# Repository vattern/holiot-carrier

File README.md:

# holiot-carrier
Carrirer board for Holyiots to fit BastardKB housings

PLEASE NOTE: These boards have to be angled when inserting them.

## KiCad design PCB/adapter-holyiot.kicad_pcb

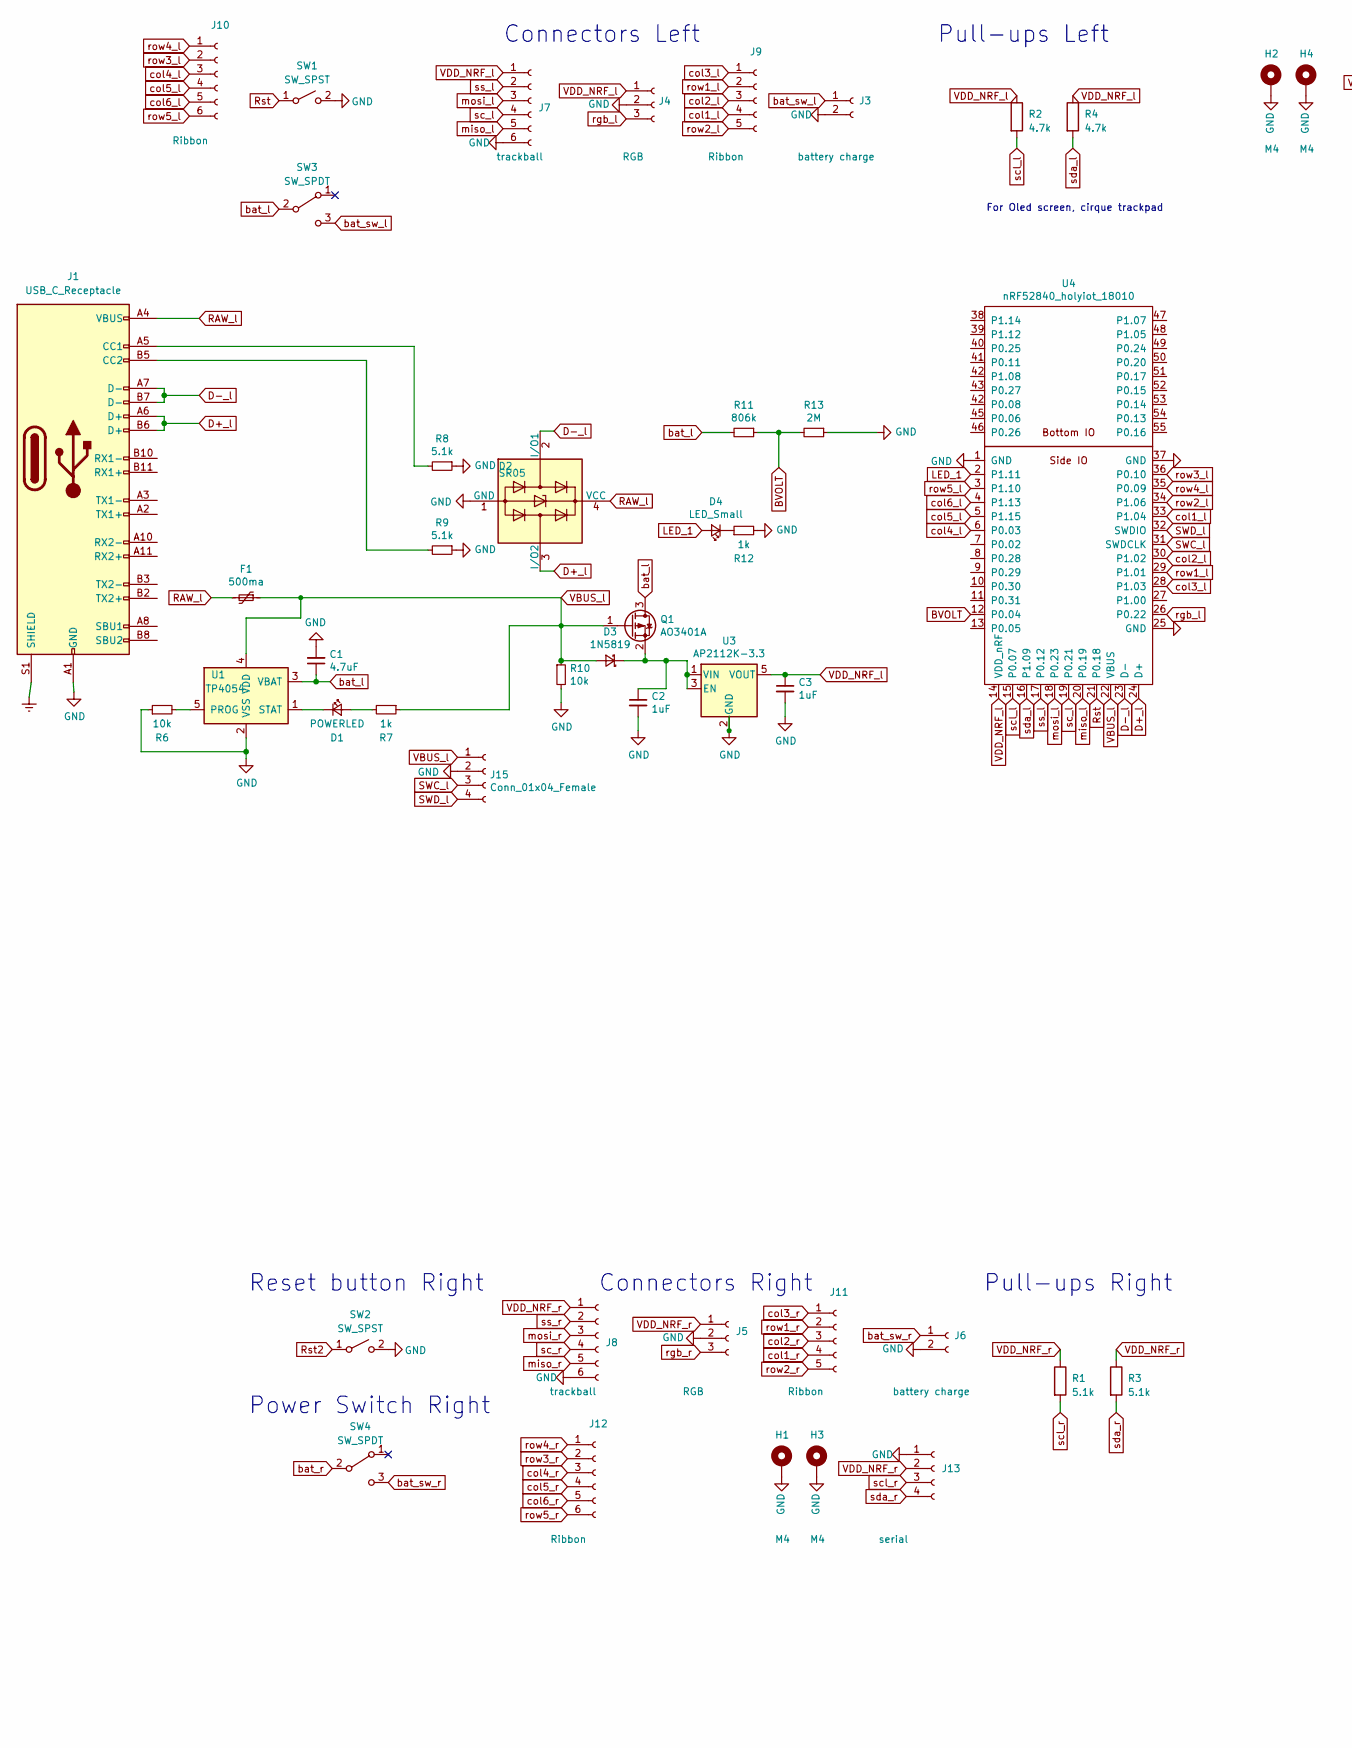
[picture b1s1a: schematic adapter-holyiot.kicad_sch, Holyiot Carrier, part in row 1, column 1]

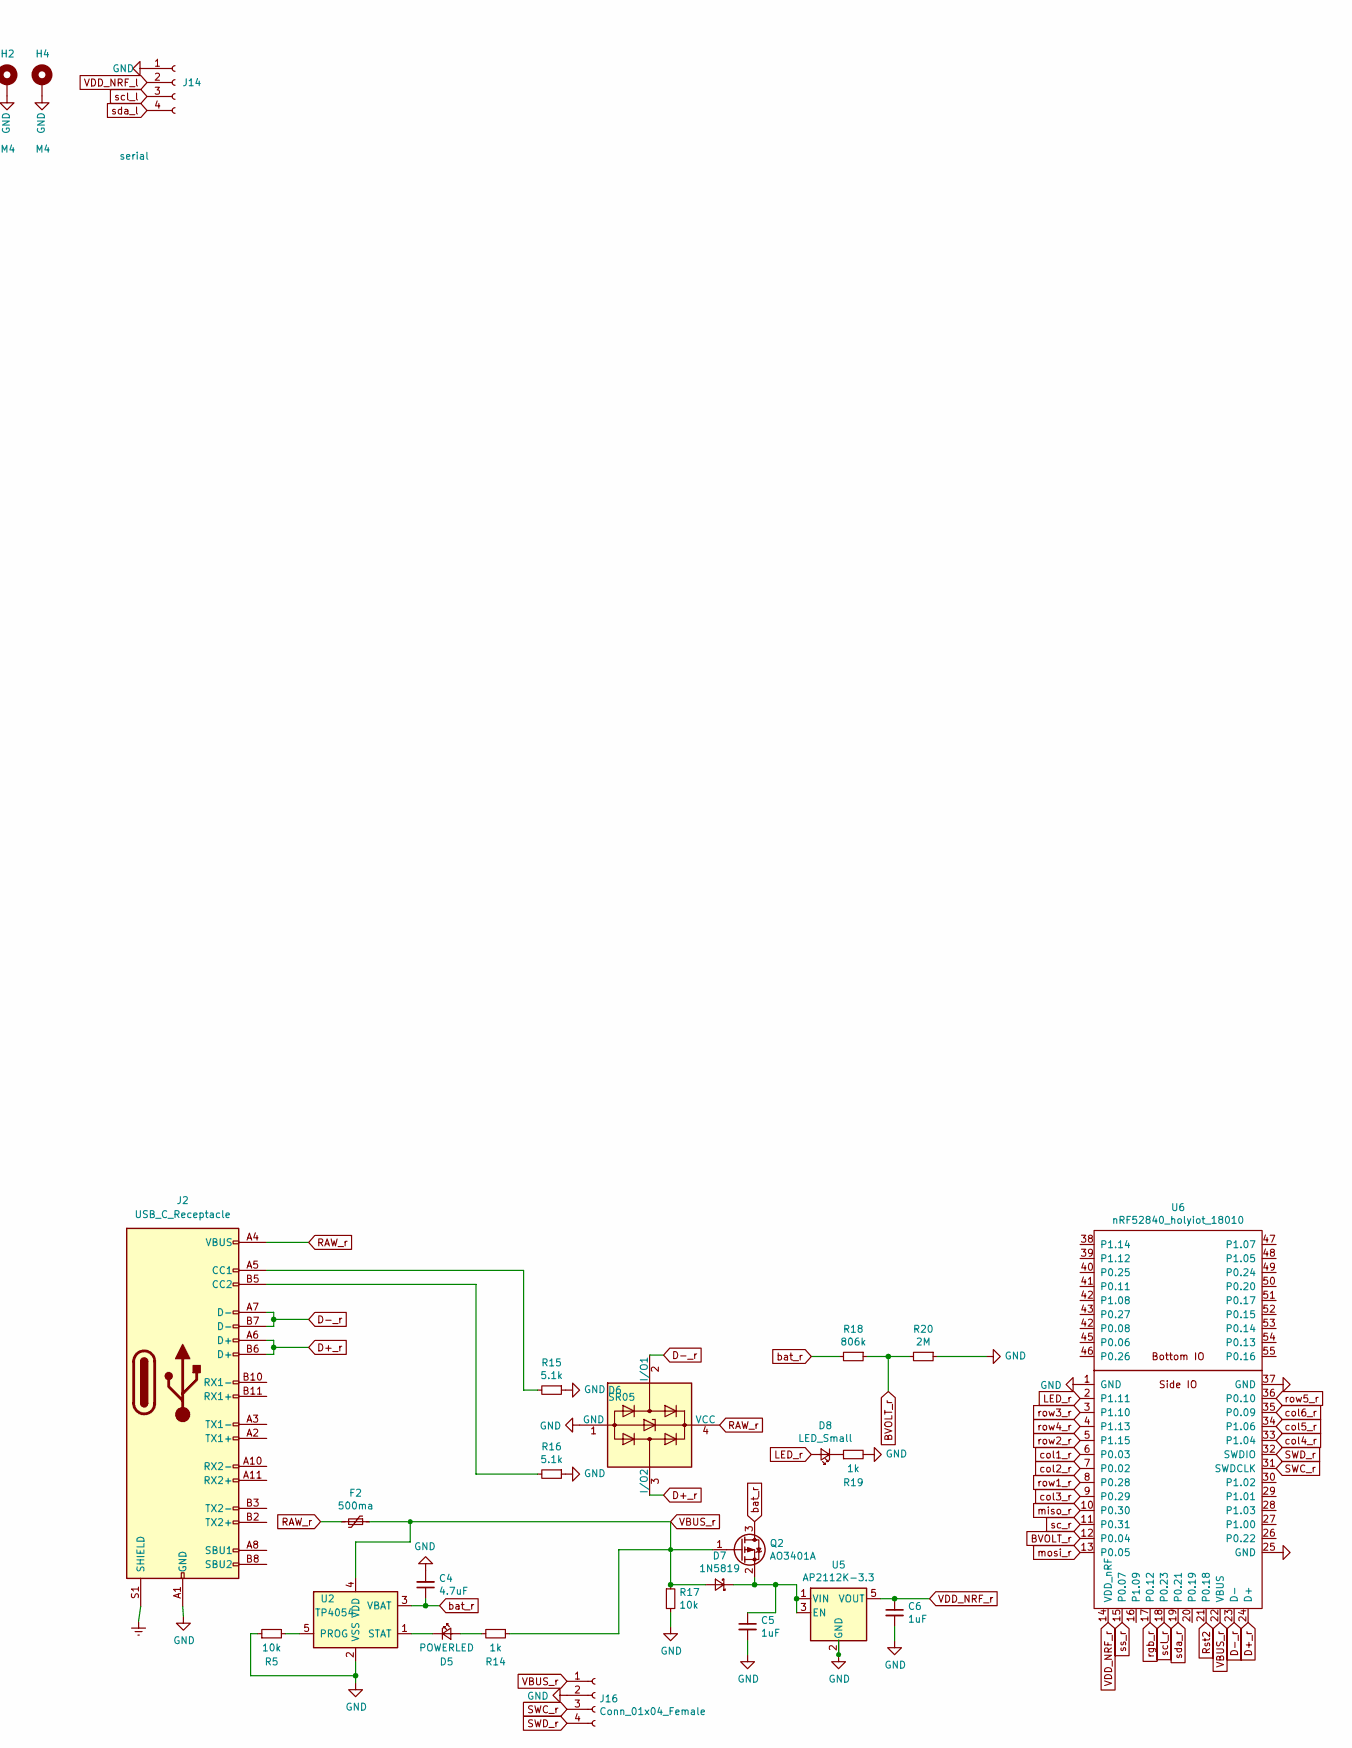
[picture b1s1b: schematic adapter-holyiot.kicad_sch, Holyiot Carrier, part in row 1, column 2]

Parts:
C1, C4: 4.7uF; C_0805_2012Metric
C2, C3, C5, C6: 1uF; C_0805_2012Metric
D1, D5: POWERLED; D_0805_2012Metric
D2, D6: SR05; SOT-143
D3, D7: 1N5819; D_SOD-123
D4, D8: LED_Small; D_0805_2012Metric
F1, F2: 500ma; Fuse_1206_3216Metric
H1, H2, H3, H4: M4; MountingHole_4mm_Pad_thin
J1, J2: USB_C_Receptacle; USB_C_Receptacle_HRO_TYPE-C-31-M-12
J3, J6: battery charge; PinHeader_1x02_P2.54mm_Vertical
J4, J5: RGB; header1x03
J7, J8: trackball; 6_PinHeader
J9, J11: Ribbon; 5_PinHeader
J10, J12: Ribbon; 6_PinHeader
J13, J14: serial; PinHeader_1x04_P2.54mm_Vertical
J15, J16: Conn_01x04_Female; PRO-HDR
Q1, Q2: AO3401A; SOT-23
R1, R3: 5.1k; R_1206_handsolder; JLCPCB BOM 1
R2, R4: 4.7k; R_1206_handsolder; JLCPCB BOM 1
R5, R6, R10, R17: 10k; R_0805_2012Metric
R7, R12, R14, R19: 1k; R_0805_2012Metric
R8, R9, R15, R16: 5.1k; R_0805_2012Metric
R11, R18: 806k; R_0805_2012Metric
R13, R20: 2M; R_0805_2012Metric
SW1, SW2: SW_SPST; PushSwitch
SW3, SW4: SW_SPDT; SW_SPDT+H-MSK12C01_hor(7pin_SMD)
U1, U2: TP4054; SOT-23-5
U3, U5: AP2112K-3.3; SOT-23-5
U4, U6: nRF52840_holyiot_18010

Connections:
BVOLT: R11.1, R13.2, U4.12 (P0.04)
BVOLT_r: R18.1, R20.2, U6.12 (P0.04)
D+_l: D2.3 (I/O2), J1.A6 (D+), J1.B6 (D+), U4.24 (D+)
D+_r: D6.3 (I/O2), J2.A6 (D+), J2.B6 (D+), U6.24 (D+)
D-_l: D2.2 (I/O1), J1.A7 (D-), J1.B7 (D-), U4.23 (D-)
D-_r: D6.2 (I/O1), J2.A7 (D-), J2.B7 (D-), U6.23 (D-)
Earth: J1.S1 (SHIELD), J2.S1 (SHIELD)
GND: C1.2, C2.2, C3.2, C4.2, C5.2, C6.2, D2.1 (GND), D6.1 (GND), H1.1, H2.1, H3.1, H4.1, J1.A1 (GND), J1.A12 (GND), J1.B1 (GND), J1.B12 (GND), J2.A1 (GND), J2.A12 (GND), J2.B1 (GND), J2.B12 (GND), J3.2, J4.2, J5.2, J6.2, J7.6, J8.6, J13.1, J14.1, J15.2, J16.2, R5.1, R6.1, R8.1, R9.1, R10.2, R12.2, R13.1, R15.1, R16.1, R17.2, R19.2, R20.1, SW1.2 (B), SW2.2 (B), U1.2 (VSS), U2.2 (VSS), U3.2 (GND), U4.1 (GND), U4.25 (GND), U4.37 (GND), U5.2 (GND), U6.1 (GND), U6.25 (GND), U6.37 (GND)
LED_1: D4.2 (A), U4.2 (P1.11)
LED_r: D8.2 (A), U6.2 (P1.11)
unnamed: C2.1, D3.1 (K), Q1.2 (S), U3.1 (VIN), U3.3 (EN)
unnamed: C5.1, D7.1 (K), Q2.2 (S), U5.1 (VIN), U5.3 (EN)
unnamed: D1.1 (K), U1.1 (STAT)
unnamed: D1.2 (A), R7.2
unnamed: D4.1 (K), R12.1
unnamed: D5.1 (K), U2.1 (STAT)
unnamed: D5.2 (A), R14.2
unnamed: D8.1 (K), R19.1
unnamed: J1.A5 (CC1), R8.2
unnamed: J1.B5 (CC2), R9.2
unnamed: J2.A5 (CC1), R15.2
unnamed: J2.B5 (CC2), R16.2
unnamed: R5.2, U2.5 (PROG)
unnamed: R6.2, U1.5 (PROG)
RAW_l: D2.4 (VCC), F1.2, J1.A4 (VBUS), J1.A9 (VBUS), J1.B4 (VBUS), J1.B9 (VBUS)
RAW_r: D6.4 (VCC), F2.2, J2.A4 (VBUS), J2.A9 (VBUS), J2.B4 (VBUS), J2.B9 (VBUS)
Rst: SW1.1 (A), U4.21 (P0.18)
Rst2: SW2.1 (A), U6.21 (P0.18)
SWC_l: J15.3, U4.31 (SWDCLK)
SWC_r: J16.3, U6.31 (SWDCLK)
SWD_l: J15.4, U4.32 (SWDIO)
SWD_r: J16.4, U6.32 (SWDIO)
VBUS_l: D3.2 (A), F1.1, J15.1, Q1.1 (G), R7.1, R10.1, U1.4 (VDD), U4.22 (VBUS)
VBUS_r: D7.2 (A), F2.1, J16.1, Q2.1 (G), R14.1, R17.1, U2.4 (VDD), U6.22 (VBUS)
VDD_NRF_l: C3.1, J4.1, J7.1, J14.2, R2.1, R4.1, U3.5 (VOUT), U4.14 (VDD_nRF)
VDD_NRF_r: C6.1, J5.1, J8.1, J13.2, R1.1, R3.1, U5.5 (VOUT), U6.14 (VDD_nRF)
bat_l: C1.1, Q1.3 (D), R11.2, SW3.2 (B), U1.3 (VBAT)
bat_r: C4.1, Q2.3 (D), R18.2, SW4.2 (B), U2.3 (VBAT)
bat_sw_l: J3.1, SW3.3 (C)
bat_sw_r: J6.1, SW4.3 (C)
col1_l: J9.4, U4.33 (P1.04)
col1_r: J11.4, U6.6 (P0.03)
col2_l: J9.3, U4.30 (P1.02)
col2_r: J11.3, U6.7 (P0.02)
col3_l: J9.1, U4.28 (P1.03)
col3_r: J11.1, U6.9 (P0.29)
col4_l: J10.3, U4.6 (P0.03)
col4_r: J12.3, U6.33 (P1.04)
col5_l: J10.4, U4.5 (P1.15)
col5_r: J12.4, U6.34 (P1.06)
col6_l: J10.5, U4.4 (P1.13)
col6_r: J12.5, U6.35 (P0.09)
miso_l: J7.5, U4.20 (P0.19)
miso_r: J8.5, U6.10 (P0.30)
mosi_l: J7.3, U4.18 (P0.23)
mosi_r: J8.3, U6.13 (P0.05)
rgb_l: J4.3, U4.26 (P0.22)
rgb_r: J5.3, U6.17 (P0.12)
row1_l: J9.2, U4.29 (P1.01)
row1_r: J11.2, U6.8 (P0.28)
row2_l: J9.5, U4.34 (P1.06)
row2_r: J11.5, U6.5 (P1.15)
row3_l: J10.2, U4.36 (P0.10)
row3_r: J12.2, U6.3 (P1.10)
row4_l: J10.1, U4.35 (P0.09)
row4_r: J12.1, U6.4 (P1.13)
row5_l: J10.6, U4.3 (P1.10)
row5_r: J12.6, U6.36 (P0.10)
sc_l: J7.4, U4.19 (P0.21)
sc_r: J8.4, U6.11 (P0.31)
scl_l: J14.3, R2.2, U4.15 (P0.07)
scl_r: J13.3, R1.2, U6.18 (P0.23)
sda_l: J14.4, R4.2, U4.16 (P1.09)
sda_r: J13.4, R3.2, U6.19 (P0.21)
ss_l: J7.2, U4.17 (P0.12)
ss_r: J8.2, U6.15 (P0.07)

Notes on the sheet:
Power Switch Right
For Oled screen, cirque trackpad
Connectors Left
Pull-ups Right
Reset button Right
Pull-ups Left
Connectors Right

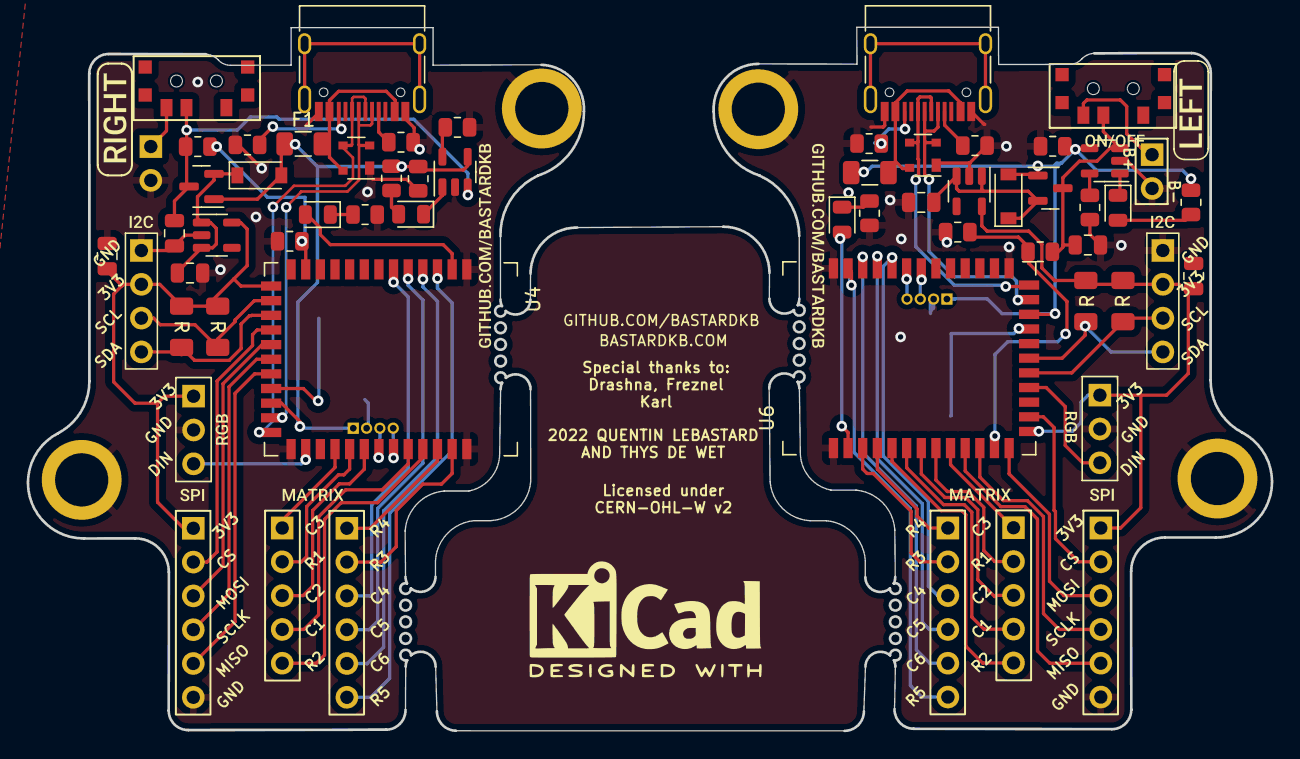
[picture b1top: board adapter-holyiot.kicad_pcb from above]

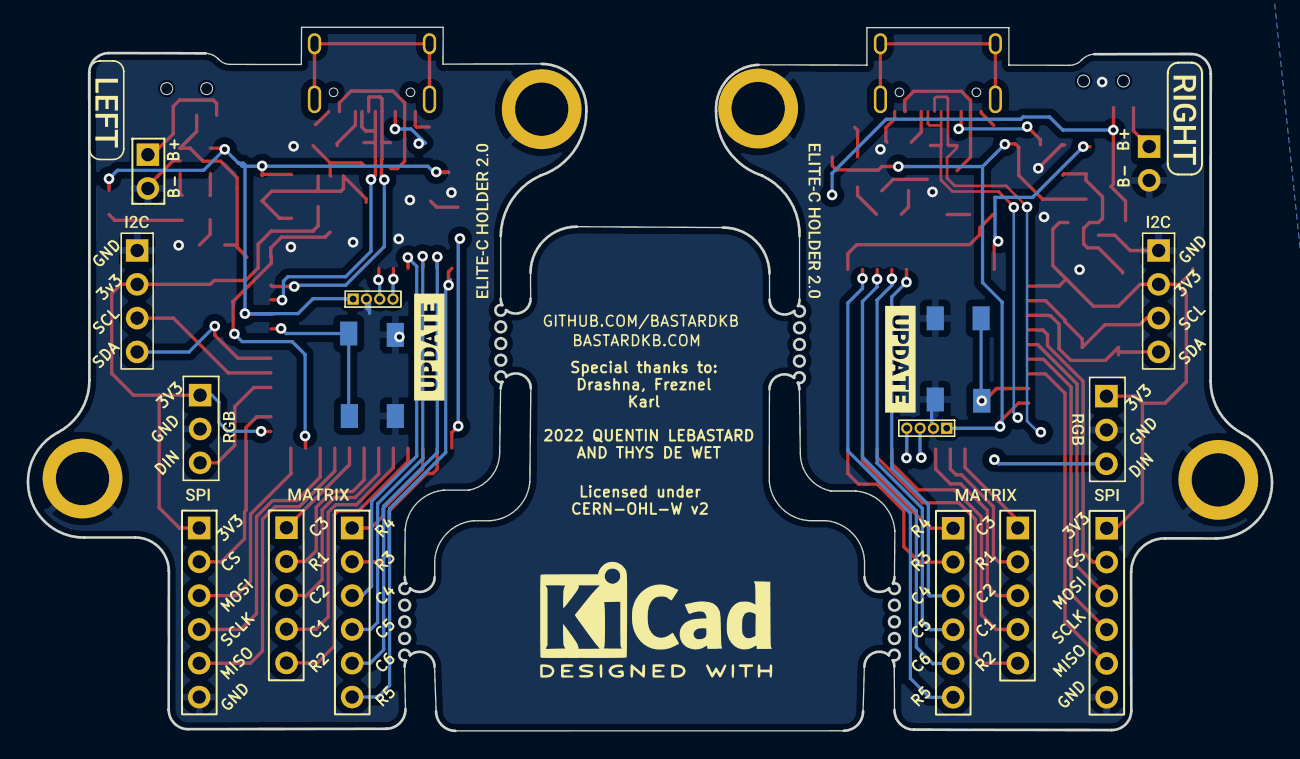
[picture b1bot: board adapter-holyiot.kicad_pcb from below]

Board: 2 copper layers, 93.5 x 52.9 mm, 95 parts (18 on the bottom side), 76 nets.

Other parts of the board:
kibuzzard-61F01A92, kibuzzard-61F01A92#2: G***; kibuzzard-61F01A92
kibuzzard-61F01B61, kibuzzard-61F01B61#2: G***; kibuzzard-61F01B61
kibuzzard-61F01C84, kibuzzard-61F01C84#2: G***; kibuzzard-61F01C84
kibuzzard-61F019CB, kibuzzard-61F019CB#2, kibuzzard-61F019CB#3, kibuzzard-61F019CB#4: G***; kibuzzard-61F019CB
kibuzzard-61F01940, kibuzzard-61F01940#2, kibuzzard-61F01940#3, kibuzzard-61F01940#4: G***; kibuzzard-61F01940
kibuzzard-61F01957, kibuzzard-61F01957#2, kibuzzard-61F01957#3, kibuzzard-61F01957#4: G***; kibuzzard-61F01957
kibuzzard-620B8D91, kibuzzard-620B8D91#2, kibuzzard-620B8D91#3, kibuzzard-620B8D91#4: G***; kibuzzard-620B8D91
kibuzzard-620B8593: G***; kibuzzard-620B8593
kibuzzard-6208E810, kibuzzard-6208E810#2: G***; kibuzzard-6208E810
kibuzzard-6208EFFE, kibuzzard-6208EFFE#2: G***; kibuzzard-6208EFFE

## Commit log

2022-06-24 Add board
2022-06-24 Add production files
2022-06-24 Add link to ZMK repo
2022-07-06 Add images
2022-10-02 Add bom.xls from last order

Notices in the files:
PCB/adapter-holyiot.kicad_pcb:
Licensed under
CERN-OHL-W v2
PCB/adapter-holyiot.kicad_sch:
Licensed under CERN-OHL-W v2
